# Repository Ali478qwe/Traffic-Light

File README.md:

## What is this project?
A miniature traffic light or a light show unit.
## Project Photos
<table>
  <tr>
    <td> </td>
    <td> </td>
    <td> </tr>
  </tr>
  <tr>
    <td> </td>
    <td> </td>
    <td> </td>
  </tr>
</table>

> [!NOTE]
> Several light-show modes are also defined in the code but are currently commented out; simply uncomment them to enjoy the visual experience.

##  Project Video

You can watch the project in action here:

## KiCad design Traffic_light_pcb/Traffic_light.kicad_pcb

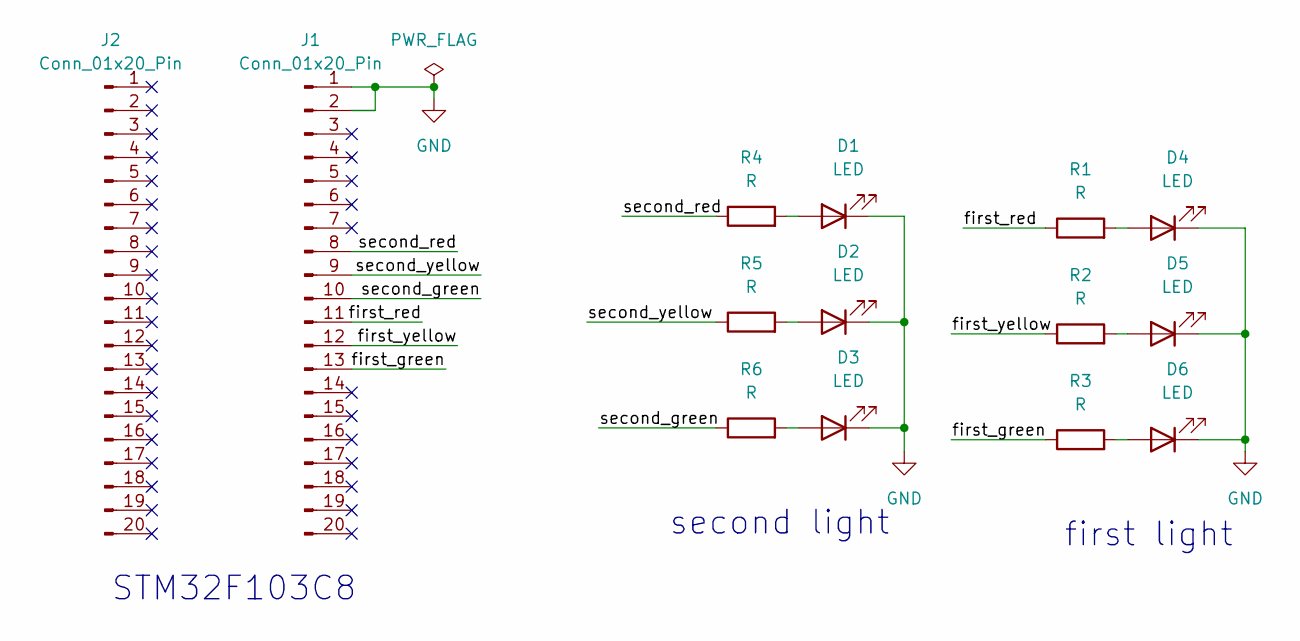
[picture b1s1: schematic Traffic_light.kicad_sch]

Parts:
D1, D2, D3, D4, D5, D6: LED; LED_D5.0mm
J1, J2: Conn_01x20_Pin; PinHeader_1x20_P2.54mm_Vertical
R1, R2, R3, R4, R5, R6: R; R_Axial_DIN0207_L6.3mm_D2.5mm_P7.62mm_Horizontal

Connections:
/first_green: J1.13, R3.1
/first_red: J1.11, R1.1
/first_yellow: J1.12, R2.1
/second_green: J1.10, R6.1
/second_red: J1.8, R4.1
/second_yellow: J1.9, R5.1
GND: D1.1 (K), D2.1 (K), D3.1 (K), D4.1 (K), D5.1 (K), D6.1 (K), J1.1, J1.2
unnamed: D1.2 (A), R4.2
unnamed: D2.2 (A), R5.2
unnamed: D3.2 (A), R6.2
unnamed: D4.2 (A), R1.2
unnamed: D5.2 (A), R2.2
unnamed: D6.2 (A), R3.2

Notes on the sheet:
second light
first light
STM32F103C8

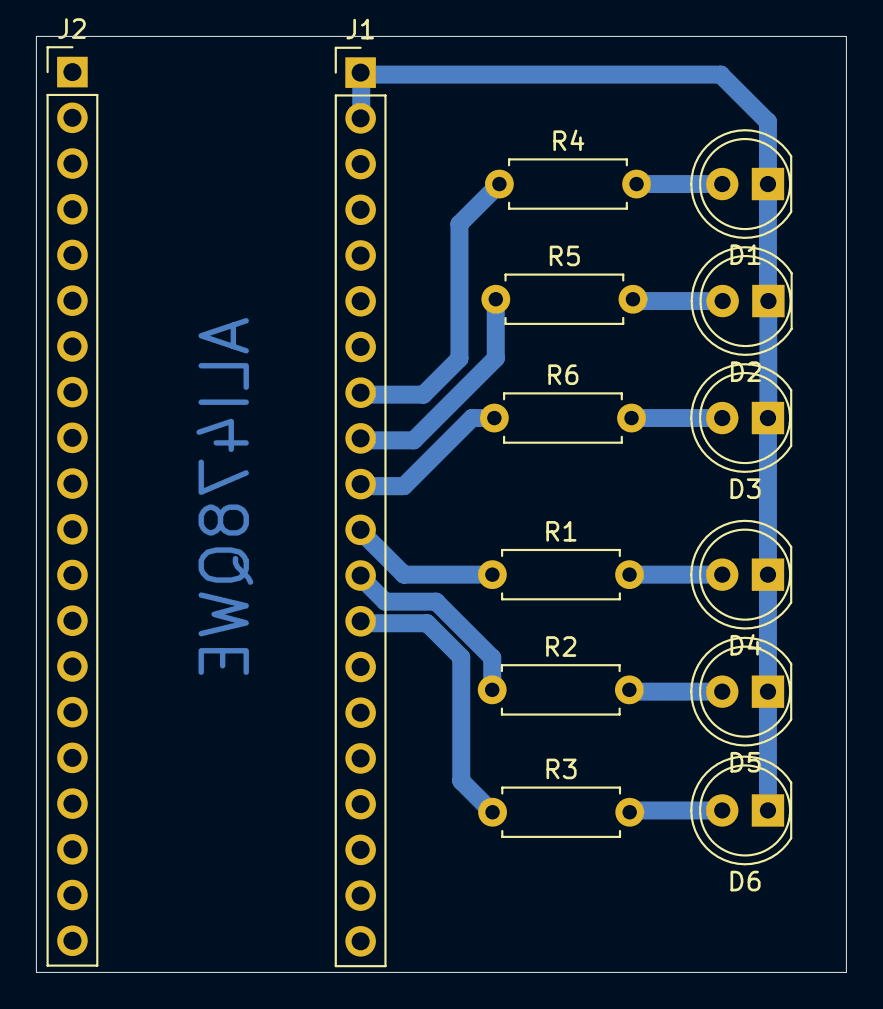
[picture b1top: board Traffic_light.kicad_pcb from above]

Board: 2 copper layers, 45.0 x 52.0 mm, 14 parts (0 on the bottom side), 13 nets.
